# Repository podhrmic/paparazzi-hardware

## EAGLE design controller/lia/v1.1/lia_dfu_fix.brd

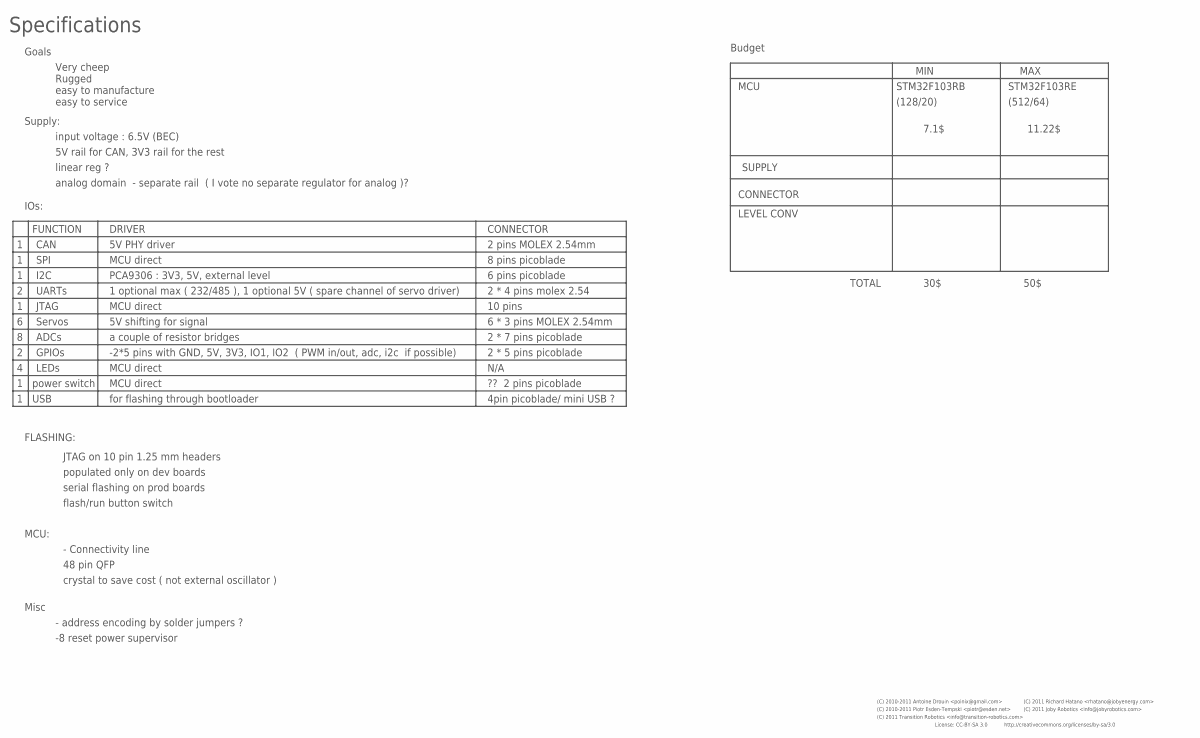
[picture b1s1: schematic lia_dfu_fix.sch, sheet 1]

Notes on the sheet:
Specifications
input voltage : 6.5V (BEC)
IOs:
CAN
SPI
I2C
UARTs
Servos
1 optional max ( 232/485 ), 1 optional 5V ( spare channel of servo driver)
5V shifting for signal
FLASHING:
JTAG on 10 pin 1.25 mm headers
populated only on dev boards
serial flashing on prod boards
flash/run button switch
PCA9306 : 3V3, 5V, external level
MCU:
- Connectivity line
48 pin QFP
crystal to save cost ( not external oscillator )
Supply:
5V rail for CAN, 3V3 rail for the rest
linear reg ?
analog domain - separate rail ( I vote no separate regulator for analog )?
Goals
Very cheep
Rugged
easy to manufacture
easy to service
Misc
- address encoding by solder jumpers ?
JTAG
ADCs
-2*5 pins with GND, 5V, 3V3, IO1, IO2 ( PWM in/out, adc, i2c if possible)
LEDs
5V PHY driver
power switch
MCU direct
a couple of resistor bridges
-8 reset power supervisor

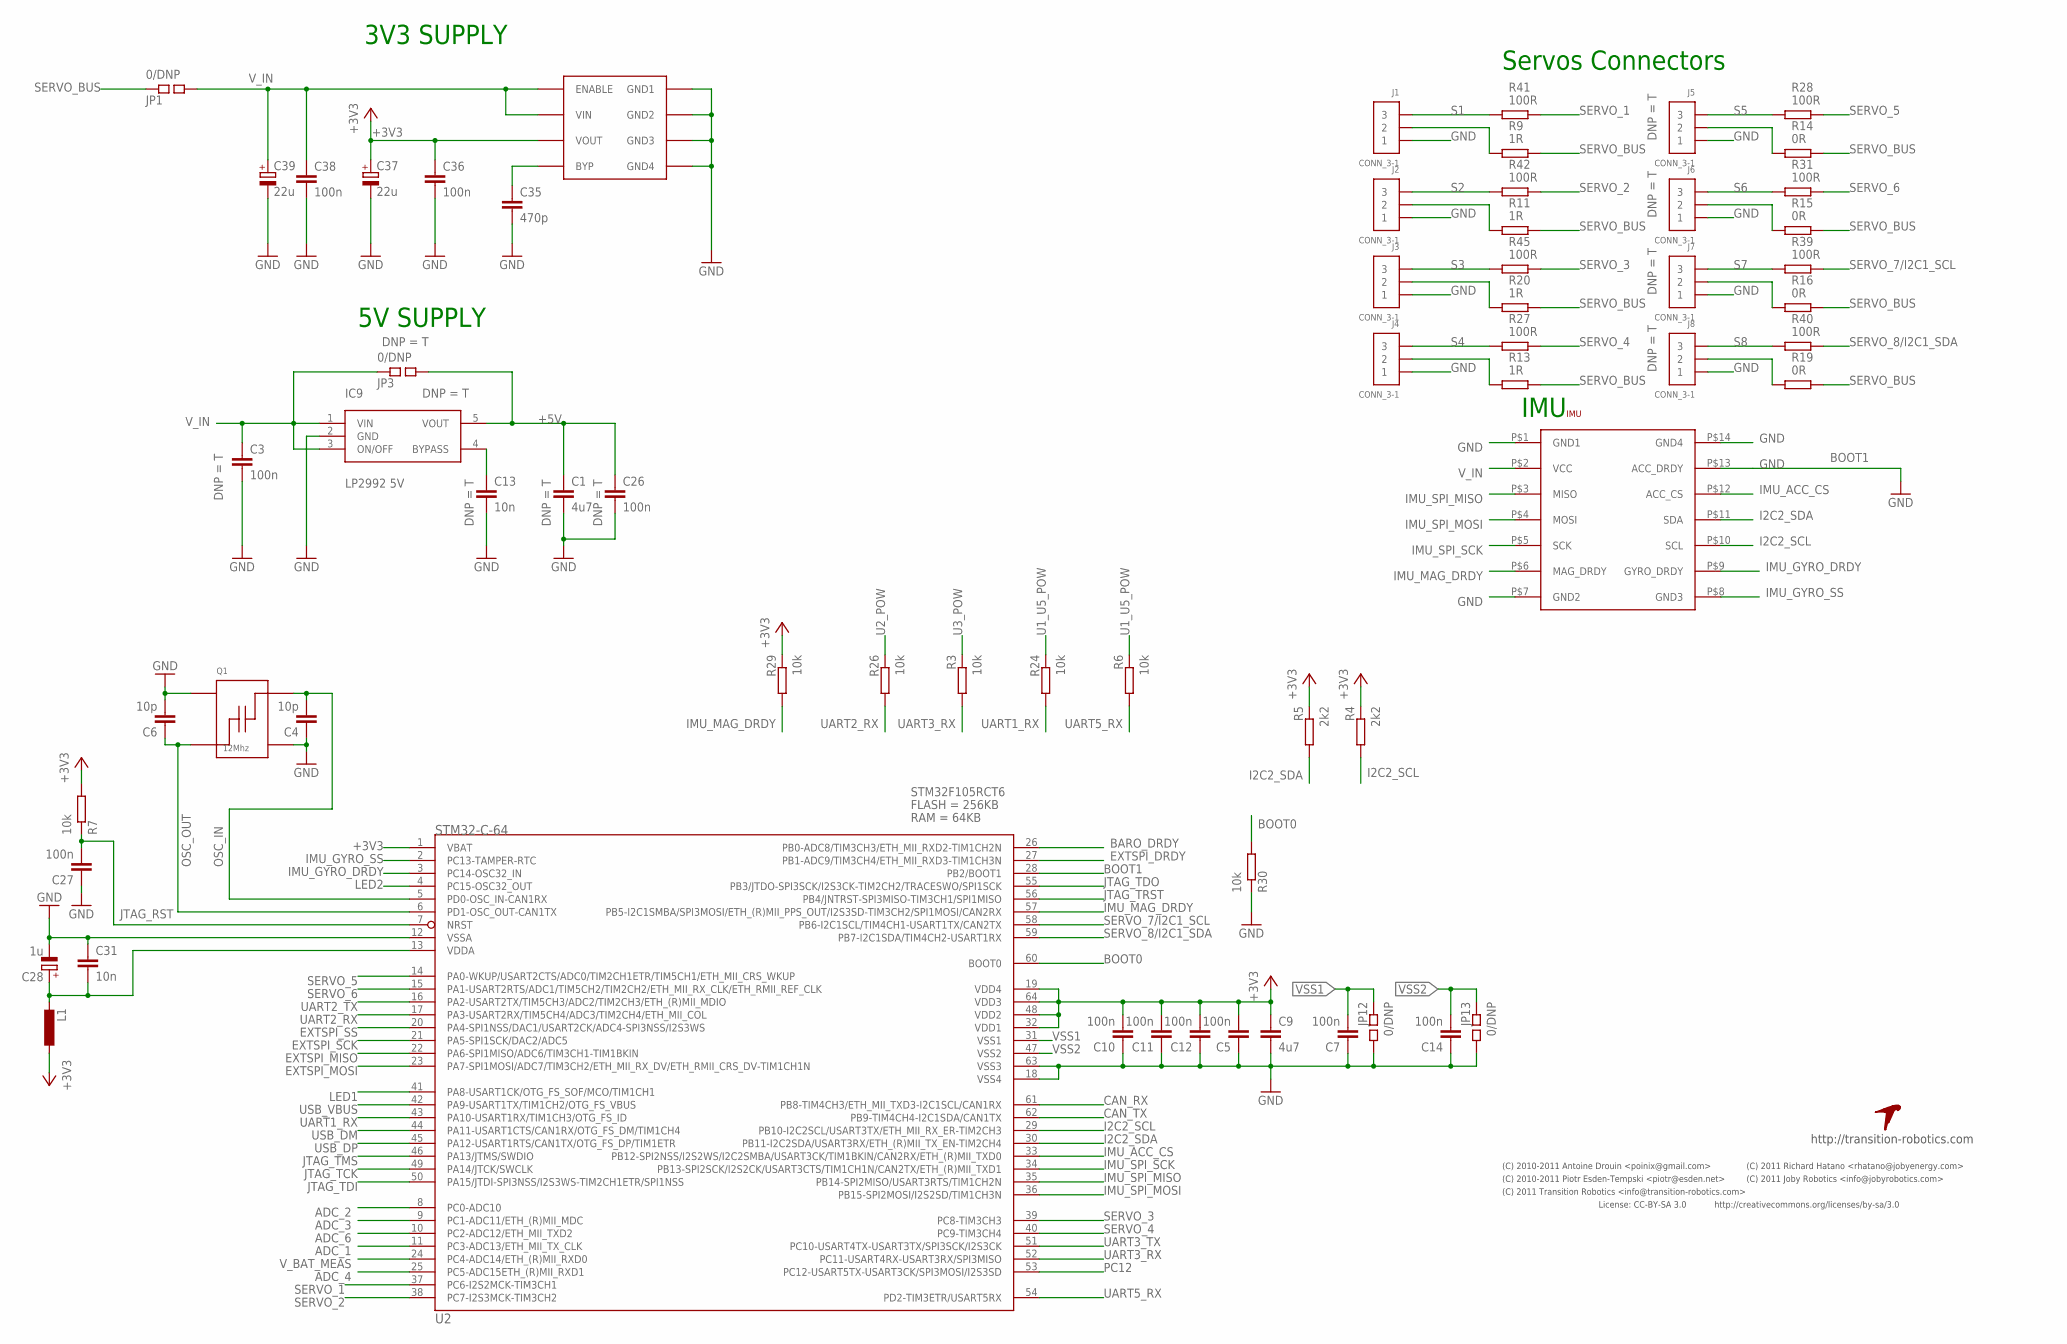
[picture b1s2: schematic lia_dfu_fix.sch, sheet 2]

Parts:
C1, C9: 4u7; 0805-CAP; PARTNO cap-cer-0805-4u7
C3, C26, C36: 100n; 0603-CAP; PARTNO cap-cer-0603-100n
C4, C6: 10p; 0402-CAP; PARTNO cap-cer-0402-10p
C5, C7, C10, C11, C12, C14, C27, C38: 100n; 0402-CAP; PARTNO cap-cer-0402-100n
C13, C31: 10n; 0402-CAP; PARTNO cap-cer-0402-10n
C28: 1u; 0603-POL-CAP; PARTNO cap-tan-0603-1u
C35: 470p; 0402-CAP; PARTNO cap-cer-0402-470p
C37, C39: 22u; 3528/B; PARTNO cap-tan-B-22u-16v
IC9: LP2992 5V; SOT23-5; PARTNO vreg-sot-23-5-5v
IMU: ASPIRIN; ASPIRIN_1; PARTNO pcb-ass-aspirin
J1, J2, J3, J4, J5, J6, J7, J8: CONN_3-1; SIP1X3_100; PARTNO conn-th-0.1in-3-2-ra
JP1, JP3, JP12, JP13: 0/DNP; 0402-SQJMP; PARTNO res-0402-0
L1: INDUCTOR-0603; 0603-IND; PARTNO ferrite-0603-600ohm
Q1: 12Mhz; ABM8; PARTNO xtal-abm8-12mhz
R3, R6, R7, R24, R26, R29, R30: 10k; 0402-RES; PARTNO res-0402-10k
R4, R5: 2k2; 0402-RES; PARTNO res-0402-2k2
R9, R11, R13, R20: 1R; 1206-RES; PARTNO res-1206-1
R14, R15, R16, R19: 0R; 1206-RES; PARTNO res-1206-0
R27, R28, R31, R39, R40, R41, R42, R45: 100R; 0402-RES; PARTNO res-0402-100
U2: STM32-C-64; LQFP64; PARTNO mcu-lqfp-64-stm32
U$1: TR-LOGO; PARTNO *
VREG1: MIC5209; SOIC8; PARTNO vreg-so8-3v3

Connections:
+3V3: C5.P$2 (2), C9.P$1 (1), C10.P$2 (2), C11.P$2 (2), C12.P$2 (2), C36.P$1 (1), C37.+, L1.P$1 (1), R4.P$1 (1), R5.P$1 (1), R7.P$2 (2), R29.P$1 (1), U2.1 (VBAT), U2.19 (VDD4), U2.32 (VDD1), U2.48 (VDD2), U2.64 (VDD3), VREG1.3 (VOUT); also elsewhere on the board
+5V: C1.P$1 (1), C26.P$1 (1), IC9.5 (VOUT), JP3.P$2 (2); also elsewhere on the board
ADC_1: U2.11 (PC3-ADC13/ETH_MII_TX_CLK); also elsewhere on the board
ADC_2: U2.8 (PC0-ADC10); also elsewhere on the board
ADC_3: U2.9 (PC1-ADC11/ETH_(R)MII_MDC); also elsewhere on the board
ADC_4: U2.25 (PC5-ADC15ETH_(R)MII_RXD1); also elsewhere on the board
ADC_6: U2.10 (PC2-ADC12/ETH_MII_TXD2); also elsewhere on the board
BARO_DRDY: U2.26 (PB0-ADC8/TIM3CH3/ETH_MII_RXD2-TIM1CH2N)
BOOT0: R30.P$2 (2), U2.60 (BOOT0); also elsewhere on the board
BOOT1: U2.28 (PB2/BOOT1)
CAN_RX: U2.61 (PB8-TIM4CH3/ETH_MII_TXD3-I2C1SCL/CAN1RX); also elsewhere on the board
CAN_TX: U2.62 (PB9-TIM4CH4-I2C1SDA/CAN1TX); also elsewhere on the board
EXTSPI_DRDY: U2.27 (PB1-ADC9/TIM3CH4/ETH_MII_RXD3-TIM1CH3N); also elsewhere on the board
EXTSPI_MISO: U2.22 (PA6-SPI1MISO/ADC6/TIM3CH1-TIM1BKIN); also elsewhere on the board
EXTSPI_MOSI: U2.23 (PA7-SPI1MOSI/ADC7/TIM3CH2/ETH_MII_RX_DV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); also elsewhere on the board
EXTSPI_SCK: U2.21 (PA5-SPI1SCK/DAC2/ADC5); also elsewhere on the board
EXTSPI_SS: U2.20 (PA4-SPI1NSS/DAC1/USART2CK/ADC4-SPI3NSS/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); also elsewhere on the board
GND: C1.P$2 (2), C3.P$2 (2), C4.P$1 (1), C5.P$1 (1), C6.P$2 (2), C7.P$1 (1), C9.P$2 (2), C10.P$1 (1), C11.P$1 (1), C12.P$1 (1), C13.P$2 (2), C14.P$1 (1), C26.P$2 (2), C27.P$1 (1), C28.-, C31.P$1 (1), C35.P$2 (2), C36.P$2 (2), C37.-, C38.P$2 (2), C39.-, IC9.2 (GND), IMU.P$1 (GND1), IMU.P$7 (GND2), IMU.P$13 (ACC_DRDY), IMU.P$14 (GND4), J1.1, J2.1, J3.1, J4.1, J5.1, J6.1, J7.1, J8.1, JP12.P$2 (2), JP13.P$2 (2), Q1.P$2, Q1.P$4, R30.P$1 (1), U2.12 (VSSA), U2.18 (VSS4), U2.63 (VSS3), VREG1.5 (GND4), VREG1.6 (GND3), VREG1.7 (GND2), VREG1.8 (GND1); also elsewhere on the board
I2C2_SCL: IMU.P$10 (SCL), R4.P$2 (2), U2.29 (PB10-I2C2SCL/USART3TX/ETH_MII_RX_ER-TIM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); also elsewhere on the board
I2C2_SDA: IMU.P$11 (SDA), R5.P$2 (2), U2.30 (PB11-I2C2SDA/USART3RX/ETH_(R)MII_TX_EN-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); also elsewhere on the board
IMU_ACC_CS: IMU.P$12 (ACC_CS), U2.33 (PB12-SPI2NSS/I2S2WS/I2C2SMBA/USART3CK/T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)
IMU_GYRO_DRDY: IMU.P$9 (GYRO_DRDY), U2.3 (PC14-OSC32_IN)
IMU_GYRO_SS: IMU.P$8 (GND3), U2.2 (PC13-TAMPER-RTC)
IMU_MAG_DRDY: IMU.P$6 (MAG_DRDY), R29.P$2 (2), U2.57 (PB5-I2C1SMBA/SPI3MOSI/ETH_(R)MII_PPS_OU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)
IMU_SPI_MISO: IMU.P$3 (MISO), U2.35 (PB14-SPI2MISO/USART3RTS/TIM1CH2N)
IMU_SPI_MOSI: IMU.P$4 (MOSI), U2.36 (PB15-SPI2MOSI/I2S2SD/TIM1CH3N)
IMU_SPI_SCK: IMU.P$5 (SCK), U2.34 (PB13-SPI2SCK/I2S2CK/USART3CTS/TIM1CH1N/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)
JTAG_RST: C27.P$2 (2), R7.P$1 (1), U2.7 (NRST); also elsewhere on the board
JTAG_TCK: U2.49 (PA14/JTCK/SWCLK); also elsewhere on the board
JTAG_TDI: U2.50 (PA15/JTDI-SPI3NSS/I2S3WS-TIM2CH1ETR/SPI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); also elsewhere on the board
JTAG_TDO: U2.55 (PB3/JTDO-SPI3SCK/I2S3CK-TIM2CH2/TRACESW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); also elsewhere on the board
JTAG_TMS: U2.46 (PA13/JTMS/SWDIO); also elsewhere on the board
JTAG_TRST: U2.56 (PB4/JNTRST-SPI3MISO-TIM3CH1/SPI1MISO); also elsewhere on the board
LED1: U2.41 (PA8-USART1CK/OTG_FS_SOF/MCO/TIM1CH1); also elsewhere on the board
LED2: U2.4 (PC15-OSC32_OUT); also elsewhere on the board
unnamed: J5.2, R14.P$1 (1)
unnamed: J6.2, R15.P$1 (1)
unnamed: C13.P$1 (1), IC9.4 (BYPASS)
unnamed: C35.P$1 (1), VREG1.4 (BYP)
unnamed: J7.2, R16.P$1 (1)
unnamed: J8.2, R19.P$1 (1)
unnamed: J4.2, R13.P$1 (1)
unnamed: J3.2, R20.P$1 (1)
unnamed: J2.2, R11.P$1 (1)
unnamed: J1.2, R9.P$1 (1)
OSC_IN: C4.P$2 (2), Q1.P$3, U2.5 (PD0-OSC_IN-CAN1RX)
OSC_OUT: C6.P$1 (1), Q1.P$1, U2.6 (PD1-OSC_OUT-CAN1TX)
PC12: U2.53 (PC12-USART5TX-USART3CK/SPI3MOSI/I2S3SD); also elsewhere on the board
S1: J1.3, R41.P$1 (1)
S2: J2.3, R42.P$1 (1)
S3: J3.3, R45.P$1 (1)
S4: J4.3, R27.P$1 (1)
S5: J5.3, R28.P$1 (1)
S6: J6.3, R31.P$1 (1)
S7: J7.3, R39.P$1 (1)
S8: J8.3, R40.P$1 (1)
SERVO_1: R41.P$2 (2), U2.37 (PC6-I2S2MCK-TIM3CH1)
SERVO_2: R42.P$2 (2), U2.38 (PC7-I2S3MCK-TIM3CH2)
SERVO_3: R45.P$2 (2), U2.39 (PC8-TIM3CH3)
SERVO_4: R27.P$2 (2), U2.40 (PC9-TIM3CH4)
SERVO_5: R28.P$2 (2), U2.14 (PA0-WKUP/USART2CTS/ADC0/TIM2CH1ETR/TIM5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)
SERVO_6: R31.P$2 (2), U2.15 (PA1-USART2RTS/ADC1/TIM5CH2/TIM2CH2/ETH_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)
SERVO_7/I2C1_SCL: R39.P$2 (2), U2.58 (PB6-I2C1SCL/TIM4CH1-USART1TX/CAN2TX); also elsewhere on the board
SERVO_8/I2C1_SDA: R40.P$2 (2), U2.59 (PB7-I2C1SDA/TIM4CH2-USART1RX); also elsewhere on the board
SERVO_BUS: JP1.P$1 (1), R9.P$2 (2), R11.P$2 (2), R13.P$2 (2), R14.P$2 (2), R15.P$2 (2), R16.P$2 (2), R19.P$2 (2), R20.P$2 (2)
U1_U5_POW: R6.P$1 (1), R24.P$1 (1); also elsewhere on the board
U2_POW: R26.P$1 (1); also elsewhere on the board
U3_POW: R3.P$1 (1); also elsewhere on the board
UART1_RX: R24.P$2 (2), U2.43 (PA10-USART1RX/TIM1CH3/OTG_FS_ID); also elsewhere on the board
UART2_RX: R26.P$2 (2), U2.17 (PA3-USART2RX/TIM5CH4/ADC3/TIM2CH4/ETH_M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); also elsewhere on the board
UART2_TX: U2.16 (PA2-USART2TX/TIM5CH3/ADC2/TIM2CH3/ETH_(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); also elsewhere on the board
UART3_RX: R3.P$2 (2), U2.52 (PC11-USART4RX-USART3RX/SPI3MISO); also elsewhere on the board
UART3_TX: U2.51 (PC10-USART4TX-USART3TX/SPI3SCK/I2S3CK); also elsewhere on the board
UART5_RX: R6.P$2 (2), U2.54 (PD2-TIM3ETR/USART5RX); also elsewhere on the board
USB_DM: U2.44 (PA11-USART1CTS/CAN1RX/OTG_FS_DM/TIM1CH4); also elsewhere on the board
USB_DP: U2.45 (PA12-USART1RTS/CAN1TX/OTG_FS_DP/TIM1ETR); also elsewhere on the board
USB_VBUS: U2.42 (PA9-USART1TX/TIM1CH2/OTG_FS_VBUS); also elsewhere on the board
VDDA: C28.+, C31.P$2 (2), L1.P$2 (2), U2.13 (VDDA)
VSS1: C7.P$2 (2), JP12.P$1 (1), U2.31 (VSS1)
VSS2: C14.P$2 (2), JP13.P$1 (1), U2.47 (VSS2)
V_BAT_MEAS: U2.24 (PC4-ADC14/ETH_(R)MII_RXD0); also elsewhere on the board
V_IN: C3.P$1 (1), C38.P$1 (1), C39.+, IC9.1 (VIN), IC9.3 (ON/OFF), IMU.P$2 (VCC), JP1.P$2 (2), JP3.P$1 (1), VREG1.1 (ENABLE), VREG1.2 (VIN); also elsewhere on the board

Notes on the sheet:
Servos Connectors
IMU
3V3 SUPPLY
5V SUPPLY
License: CC-BY-SA 3.0
http://creativecommons.org/licenses/by-sa/3.0
(C) 2010-2011 Piotr Esden-Tempski <piotr@esden.net>
(C) 2010-2011 Antoine Drouin <poinix@gmail.com>
(C) 2011 Richard Hatano <rhatano@jobyenergy.com>
(C) 2011 Joby Robotics <info@jobyrobotics.com>
http://transition-robotics.com
(C) 2011 Transition Robotics <info@transition-robotics.com>
BOOT1

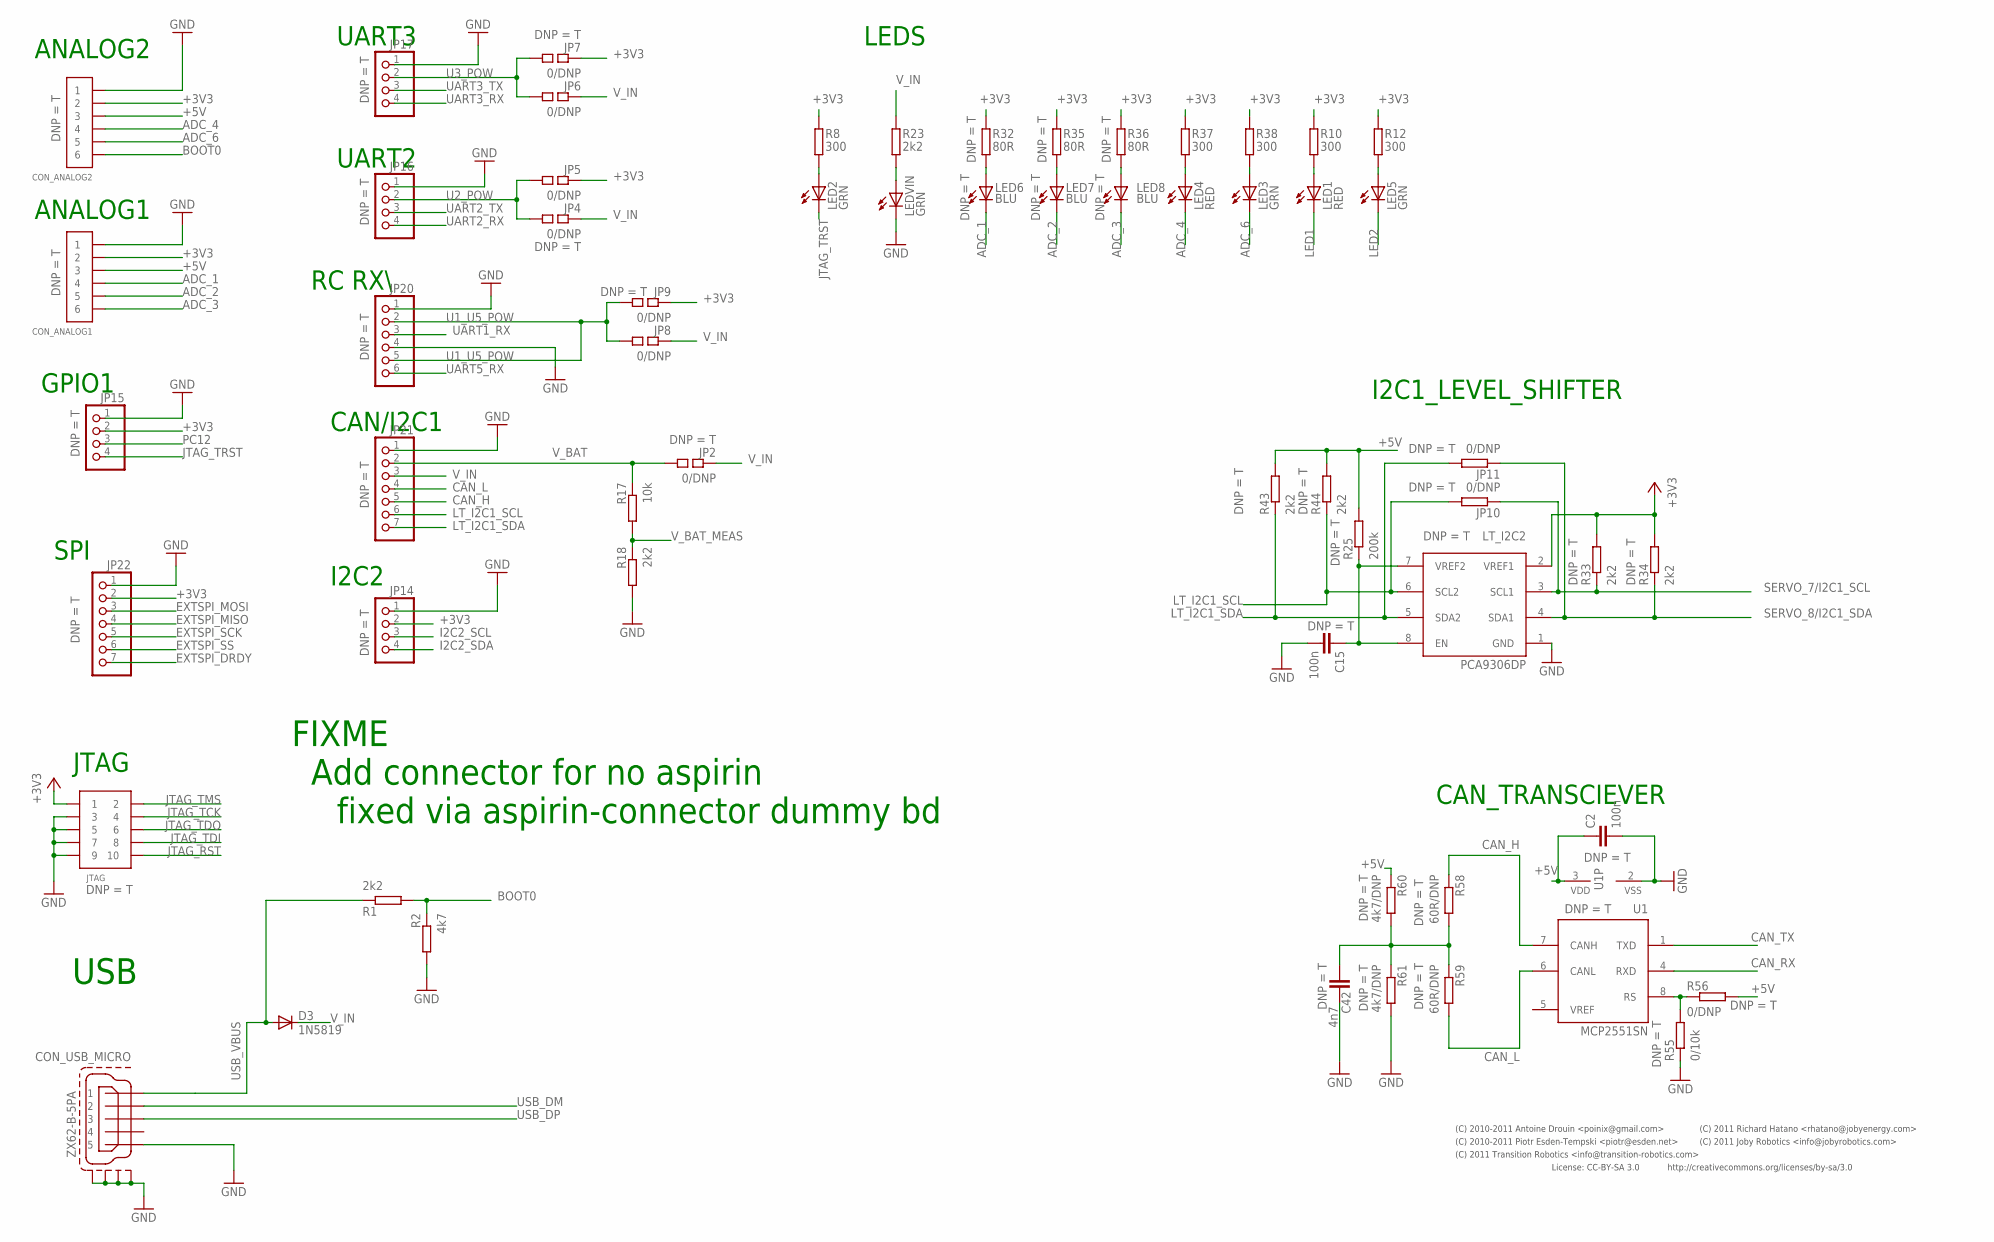
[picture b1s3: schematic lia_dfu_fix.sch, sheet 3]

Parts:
C2, C15: 100n; 0402-CAP; PARTNO cap-cer-0402-100n
C42: 4n7; 0603-CAP; PARTNO cap-cer-0603-4n7
CON_ANALOG1, CON_ANALOG2: CONN_6-1-53398; PB-53398-06; PARTNO conn-picoblade-smd-0.05in-6-vert
CON_USB_MICRO: ZX62-B-5PA; PARTNO conn-smd-usb-micro-b
D3: 1N5819; MICROMELF-R; PARTNO diode-schottky-1608
JP2, JP4, JP5, JP6, JP7, JP8, JP9: 0/DNP; 0402-SQJMP; PARTNO res-0402-0
JP10, JP11: 0/DNP; 0603-RES; PARTNO res-0603-0
JP14, JP15, JP16, JP17: PINHD-1X4; 1X04; PARTNO conn-th-0.1in-4-1
JP20: PINHD-1X6; 1X06; PARTNO conn-th-0.1in-6-1
JP21, JP22: PINHD-1X7; 1X07; PARTNO conn-th-0.1in-7-1
JTAG: PIN_HDR_EDG_1.27MM_5-2; FTSH-105-DV; PARTNO conn-smd-0.05in-5-2
LED1, LED4: RED; 0402-LED; PARTNO led-0402-red
LED2, LED3, LED5: GRN; 0402-LED; PARTNO led-0402-green
LED6, LED7, LED8: BLU; 0402-LED; PARTNO led-0402-blue
LEDVIN: GRN; 0402-LED; PARTNO led-0402-green
LT_I2C2: PCA9306DP; TSSOP_B3; PARTNO ic-tssop8-level-trans
R1, R18, R23, R33, R34: 2k2; 0402-RES; PARTNO res-0402-2k2
R2: 4k7; 0402-RES; PARTNO res-0402-2k2
R8, R10, R12, R37, R38: 300; 0402-RES; PARTNO res-0402-300
R17: 10k; 0402-RES; PARTNO res-0402-10k
R25: 200k; 0402-RES; PARTNO res-0402-200k
R32, R35, R36: 80R; 0402-RES; PARTNO res-0402-80
R43, R44: 2k2; 0402-RES; PARTNO res-0402-1k5
R55: 0/10k; 0402-RES; PARTNO res-0402-10k
R56: 0/DNP; 0402-RES; PARTNO res-0402-0
R58, R59: 60R/DNP; 0402-RES; PARTNO res-0402-60.4
R60, R61: 4k7/DNP; 0402-RES; PARTNO res-0402-4k7
U1: MCP2551SN; SO-08; PARTNO ic-so8-can

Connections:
+3V3: CON_ANALOG1.2, CON_ANALOG2.2, JP5.P$1 (1), JP7.P$1 (1), JP9.P$1 (1), JP14.2, JP15.2, JP22.2, JTAG.1, LT_I2C2.2 (VREF1), R8.P$2 (2), R10.P$2 (2), R12.P$2 (2), R32.P$2 (2), R33.P$2 (2), R34.P$2 (2), R35.P$2 (2), R36.P$2 (2), R37.P$2 (2), R38.P$2 (2); also elsewhere on the board
+5V: C2.P$1 (1), CON_ANALOG1.3, CON_ANALOG2.3, R25.P$2 (2), R43.P$2 (2), R44.P$2 (2), R56.P$2 (2), R60.P$1 (1), U1.3 (VDD); also elsewhere on the board
ADC_1: CON_ANALOG1.4, LED6.C; also elsewhere on the board
ADC_2: CON_ANALOG1.5, LED7.C; also elsewhere on the board
ADC_3: CON_ANALOG1.6, LED8.C; also elsewhere on the board
ADC_4: CON_ANALOG2.4, LED4.C; also elsewhere on the board
ADC_6: CON_ANALOG2.5, LED3.C; also elsewhere on the board
BOOT0: CON_ANALOG2.6, R1.P$2 (2), R2.P$1 (1); also elsewhere on the board
CAN_CENTER: C42.P$2 (2), R58.P$2 (2), R59.P$1 (1), R60.P$2 (2), R61.P$1 (1)
CAN_H: JP21.5, R58.P$1 (1), U1.7 (CANH)
CAN_L: JP21.4, R59.P$2 (2), U1.6 (CANL)
CAN_RX: U1.4 (RXD); also elsewhere on the board
CAN_TX: U1.1 (TXD); also elsewhere on the board
EXTSPI_DRDY: JP22.7; also elsewhere on the board
EXTSPI_MISO: JP22.4; also elsewhere on the board
EXTSPI_MOSI: JP22.3; also elsewhere on the board
EXTSPI_SCK: JP22.5; also elsewhere on the board
EXTSPI_SS: JP22.6; also elsewhere on the board
GND: C2.P$2 (2), C15.P$2 (2), C42.P$1 (1), CON_ANALOG1.1, CON_ANALOG2.1, CON_USB_MICRO.GND_LEFT (S1), CON_USB_MICRO.GND_RIGHT (S2), CON_USB_MICRO.GND_UP_LEFT (S3), CON_USB_MICRO.GND_UP_RIGHT (S4), CON_USB_MICRO.PIN_5 (5), JP14.1, JP15.1, JP16.1, JP17.1, JP20.1, JP20.4, JP21.1, JP22.1, JTAG.3, JTAG.5, JTAG.7, JTAG.9, LEDVIN.C, LT_I2C2.1 (GND), R2.P$2 (2), R18.P$2 (2), R55.P$1 (1), R61.P$2 (2), U1.2 (VSS); also elsewhere on the board
I2C2_SCL: JP14.3; also elsewhere on the board
I2C2_SDA: JP14.4; also elsewhere on the board
JTAG_RST: JTAG.10; also elsewhere on the board
JTAG_TCK: JTAG.4; also elsewhere on the board
JTAG_TDI: JTAG.8; also elsewhere on the board
JTAG_TDO: JTAG.6; also elsewhere on the board
JTAG_TMS: JTAG.2; also elsewhere on the board
JTAG_TRST: JP15.4, LED2.C; also elsewhere on the board
LED1: LED1.C; also elsewhere on the board
LED2: LED5.C; also elsewhere on the board
LT_I2C1_SCL: JP10.P$2 (2), JP21.6, LT_I2C2.6 (SCL2), R44.P$1 (1)
LT_I2C1_SDA: JP11.P$2 (2), JP21.7, LT_I2C2.5 (SDA2), R43.P$1 (1)
unnamed: R55.P$2 (2), R56.P$1 (1), U1.8 (RS)
unnamed: LED1.A, R10.P$1 (1)
unnamed: LED6.A, R32.P$1 (1)
unnamed: C15.P$1 (1), LT_I2C2.7 (VREF2), LT_I2C2.8 (EN), R25.P$1 (1)
unnamed: LED7.A, R35.P$1 (1)
unnamed: LED2.A, R8.P$1 (1)
unnamed: LED8.A, R36.P$1 (1)
unnamed: LEDVIN.A, R23.P$1 (1)
unnamed: LED5.A, R12.P$1 (1)
unnamed: LED4.A, R37.P$1 (1)
unnamed: LED3.A, R38.P$1 (1)
PC12: JP15.3; also elsewhere on the board
SERVO_7/I2C1_SCL: JP10.P$1 (1), LT_I2C2.3 (SCL1), R33.P$1 (1); also elsewhere on the board
SERVO_8/I2C1_SDA: JP11.P$1 (1), LT_I2C2.4 (SDA1), R34.P$1 (1); also elsewhere on the board
U1_U5_POW: JP8.P$2 (2), JP9.P$2 (2), JP20.2, JP20.5; also elsewhere on the board
U2_POW: JP4.P$2 (2), JP5.P$2 (2), JP16.2; also elsewhere on the board
U3_POW: JP6.P$2 (2), JP7.P$2 (2), JP17.2; also elsewhere on the board
UART1_RX: JP20.3; also elsewhere on the board
UART2_RX: JP16.4; also elsewhere on the board
UART2_TX: JP16.3; also elsewhere on the board
UART3_RX: JP17.4; also elsewhere on the board
UART3_TX: JP17.3; also elsewhere on the board
UART5_RX: JP20.6; also elsewhere on the board
USB_DM: CON_USB_MICRO.PIN_2 (2); also elsewhere on the board
USB_DP: CON_USB_MICRO.PIN_3 (3); also elsewhere on the board
USB_VBUS: CON_USB_MICRO.PIN_1 (1), D3.A, R1.P$1 (1); also elsewhere on the board
VREF: U1.5 (VREF)
V_BAT: JP2.P$2 (2), JP21.2, R17.P$1 (1)
V_BAT_MEAS: R17.P$2 (2), R18.P$1 (1); also elsewhere on the board
V_IN: D3.C, JP2.P$1 (1), JP4.P$1 (1), JP6.P$1 (1), JP8.P$1 (1), JP21.3, R23.P$2 (2); also elsewhere on the board

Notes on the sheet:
SPI
I2C2
ANALOG2
ANALOG1
GPIO1
UART3
UART2
RC RX\
CAN/I2C1
I2C1_LEVEL_SHIFTER
CAN_TRANSCIEVER
LEDS
USB
JTAG
FIXME
Add connector for no aspirin
fixed via aspirin-connector dummy bd
License: CC-BY-SA 3.0
http://creativecommons.org/licenses/by-sa/3.0
(C) 2010-2011 Piotr Esden-Tempski <piotr@esden.net>
(C) 2010-2011 Antoine Drouin <poinix@gmail.com>
(C) 2011 Richard Hatano <rhatano@jobyenergy.com>
(C) 2011 Joby Robotics <info@jobyrobotics.com>
(C) 2011 Transition Robotics <info@transition-robotics.com>

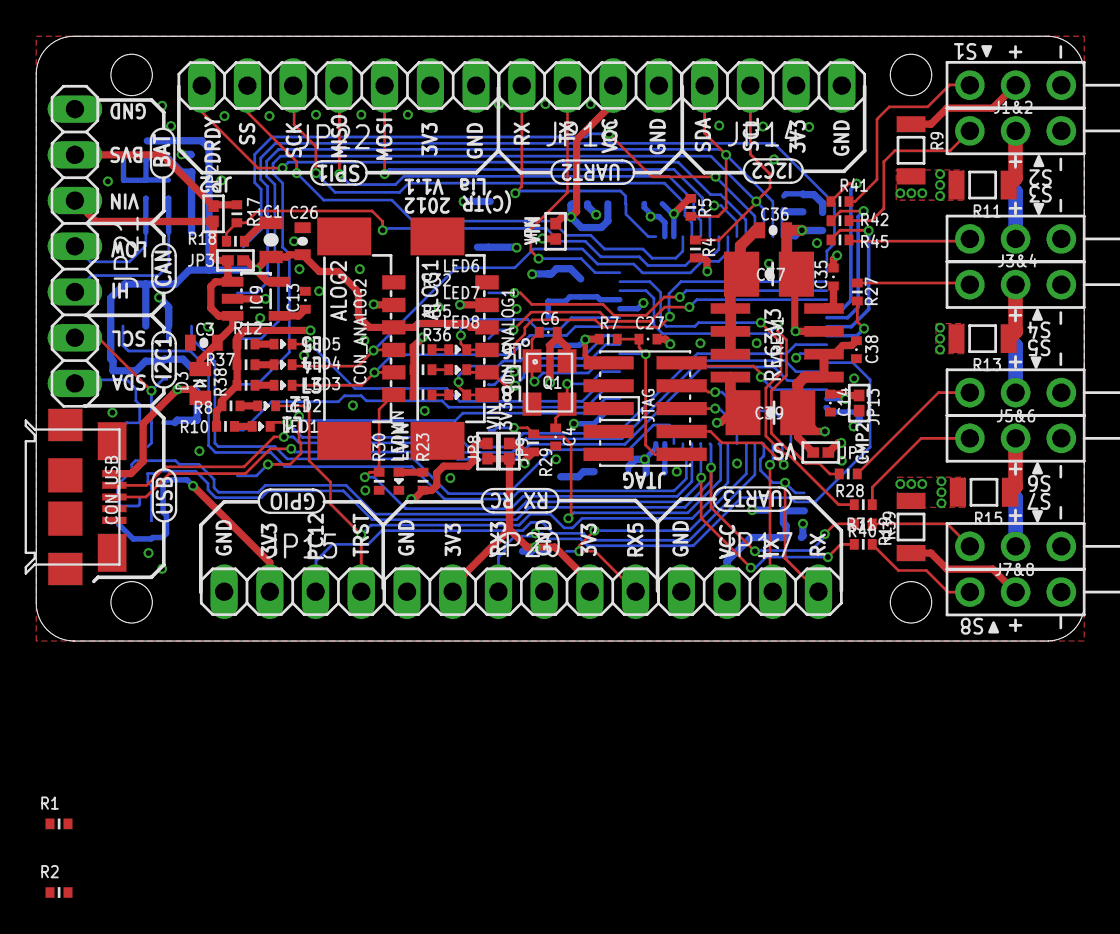
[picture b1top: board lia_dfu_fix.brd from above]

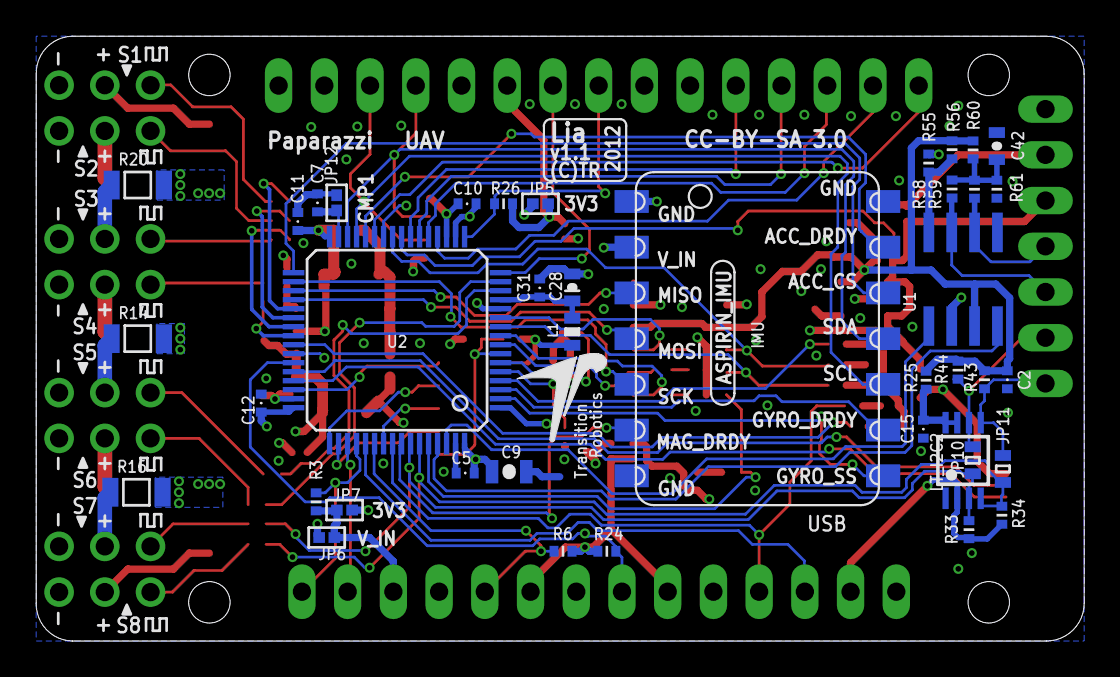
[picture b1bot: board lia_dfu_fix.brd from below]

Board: 4 copper layers, 58.2 x 33.6 mm, 124 parts (41 on the bottom side), 97 nets.

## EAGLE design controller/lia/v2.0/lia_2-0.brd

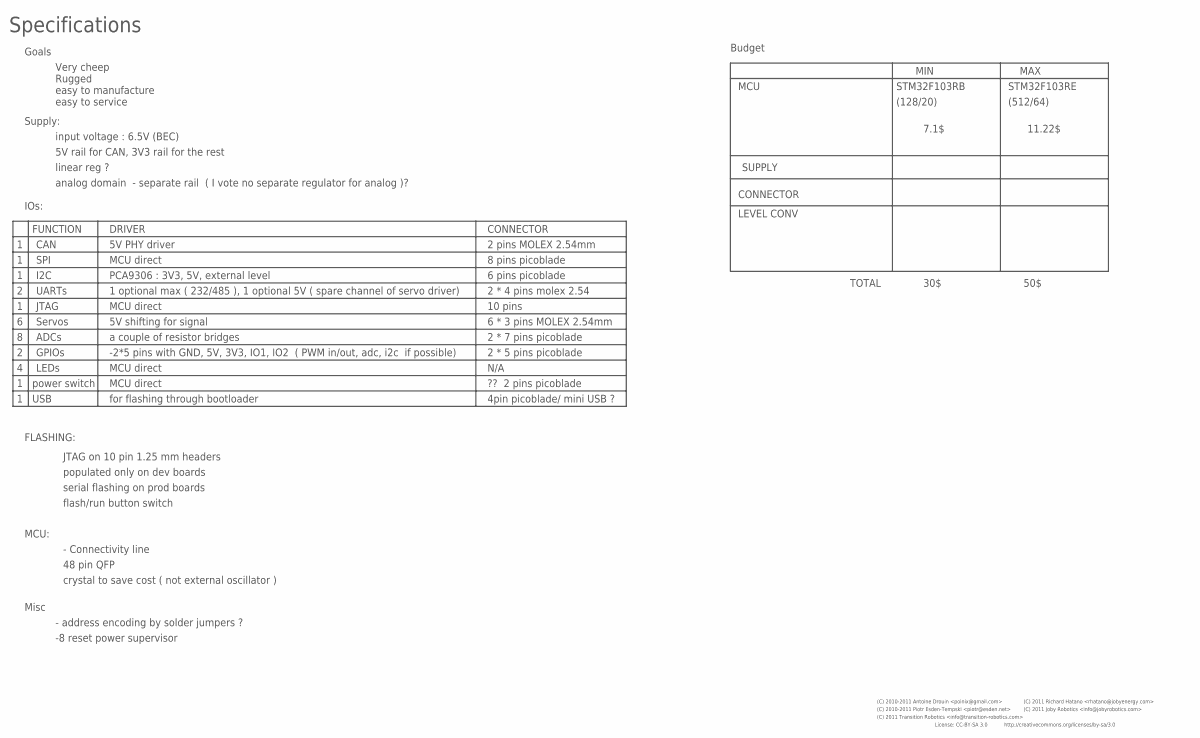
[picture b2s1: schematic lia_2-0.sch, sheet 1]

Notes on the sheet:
Specifications
input voltage : 6.5V (BEC)
IOs:
CAN
SPI
I2C
UARTs
Servos
1 optional max ( 232/485 ), 1 optional 5V ( spare channel of servo driver)
5V shifting for signal
FLASHING:
JTAG on 10 pin 1.25 mm headers
populated only on dev boards
serial flashing on prod boards
flash/run button switch
PCA9306 : 3V3, 5V, external level
MCU:
- Connectivity line
48 pin QFP
crystal to save cost ( not external oscillator )
Supply:
5V rail for CAN, 3V3 rail for the rest
linear reg ?
analog domain - separate rail ( I vote no separate regulator for analog )?
Goals
Very cheep
Rugged
easy to manufacture
easy to service
Misc
- address encoding by solder jumpers ?
JTAG
ADCs
-2*5 pins with GND, 5V, 3V3, IO1, IO2 ( PWM in/out, adc, i2c if possible)
LEDs
5V PHY driver
power switch
MCU direct
a couple of resistor bridges
-8 reset power supervisor

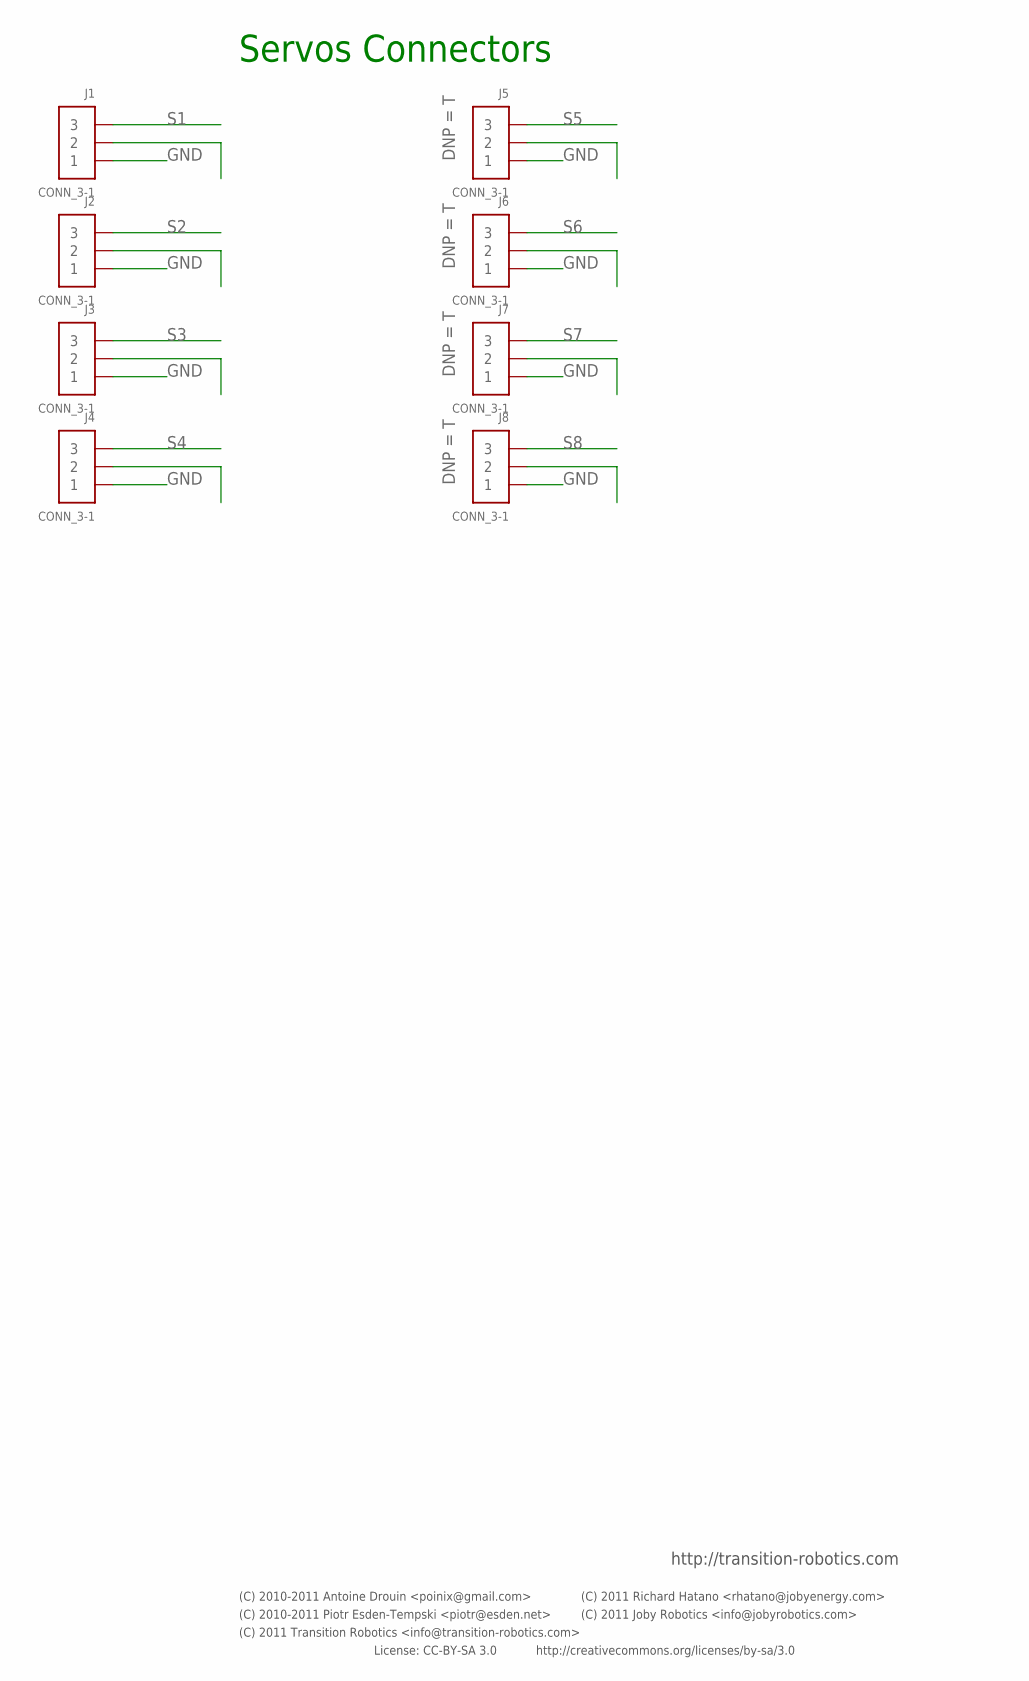
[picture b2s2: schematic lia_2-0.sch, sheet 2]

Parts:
J1, J2, J3, J4, J5, J6, J7, J8: CONN_3-1; SIP1X3_100; PARTNO conn-th-0.1in-3-2-ra

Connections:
GND: J1.1, J2.1, J3.1, J4.1, J5.1, J6.1, J7.1, J8.1; also elsewhere on the board
S1: J1.3
S2: J2.3
S3: J3.3
S4: J4.3
S5: J5.3
S6: J6.3
S7: J7.3
S8: J8.3

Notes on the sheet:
Servos Connectors
License: CC-BY-SA 3.0
http://creativecommons.org/licenses/by-sa/3.0
(C) 2010-2011 Piotr Esden-Tempski <piotr@esden.net>
(C) 2010-2011 Antoine Drouin <poinix@gmail.com>
(C) 2011 Richard Hatano <rhatano@jobyenergy.com>
(C) 2011 Joby Robotics <info@jobyrobotics.com>
http://transition-robotics.com
(C) 2011 Transition Robotics <info@transition-robotics.com>

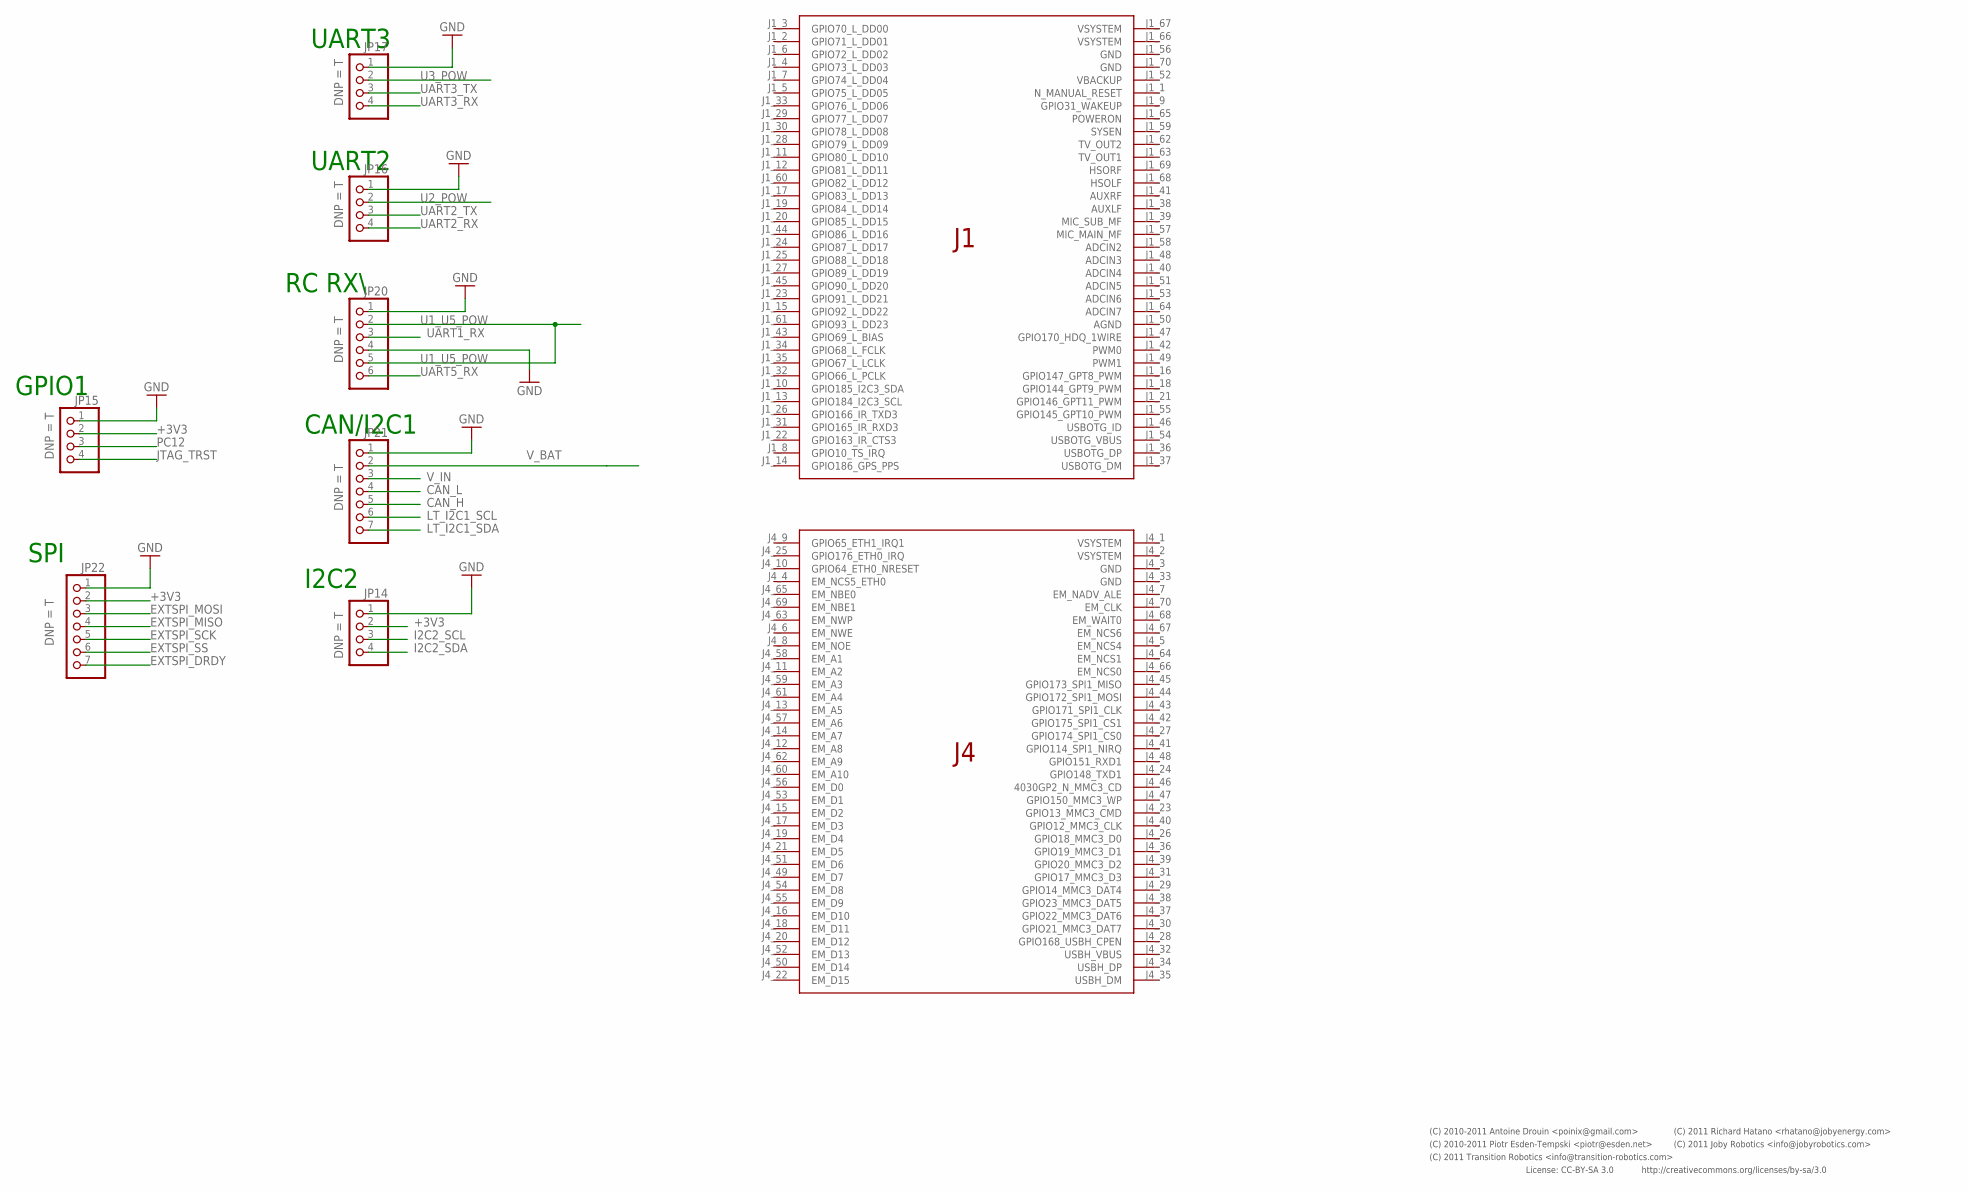
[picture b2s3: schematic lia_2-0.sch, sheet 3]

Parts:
JP14, JP15, JP16, JP17: PINHD-1X4; 1X04; PARTNO conn-th-0.1in-4-1
JP20: PINHD-1X6; 1X06; PARTNO conn-th-0.1in-6-1
JP21, JP22: PINHD-1X7; 1X07; PARTNO conn-th-0.1in-7-1
U$2: OVERO

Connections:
+3V3: JP14.2, JP15.2, JP22.2
CAN_H: JP21.5
CAN_L: JP21.4
EXTSPI_DRDY: JP22.7
EXTSPI_MISO: JP22.4
EXTSPI_MOSI: JP22.3
EXTSPI_SCK: JP22.5
EXTSPI_SS: JP22.6
GND: JP14.1, JP15.1, JP16.1, JP17.1, JP20.1, JP20.4, JP21.1, JP22.1; also elsewhere on the board
I2C2_SCL: JP14.3
I2C2_SDA: JP14.4
JTAG_TRST: JP15.4
LT_I2C1_SCL: JP21.6
LT_I2C1_SDA: JP21.7
PC12: JP15.3
U1_U5_POW: JP20.2, JP20.5
U2_POW: JP16.2
U3_POW: JP17.2
UART1_RX: JP20.3
UART2_RX: JP16.4
UART2_TX: JP16.3
UART3_RX: JP17.4
UART3_TX: JP17.3
UART5_RX: JP20.6
V_BAT: JP21.2
V_IN: JP21.3

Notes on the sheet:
SPI
I2C2
GPIO1
UART3
UART2
RC RX\
CAN/I2C1
License: CC-BY-SA 3.0
http://creativecommons.org/licenses/by-sa/3.0
(C) 2010-2011 Piotr Esden-Tempski <piotr@esden.net>
(C) 2010-2011 Antoine Drouin <poinix@gmail.com>
(C) 2011 Richard Hatano <rhatano@jobyenergy.com>
(C) 2011 Joby Robotics <info@jobyrobotics.com>
(C) 2011 Transition Robotics <info@transition-robotics.com>

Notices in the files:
controller/lia/v1.1/lia_dfu_fix.brd:
Licensed under:
(C) 2010-2012 Piotr Esden-Tempski
(C) 2011-2012 Transition Robotics
